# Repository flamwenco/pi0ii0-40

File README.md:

# pi0ii0-40
Open source, RP2040 based pcb for the [M0ii040](https://booth.pm/ja/items/4407257).

Supported layout options:

## Production files

The current version of this pcb that supports all above layouts has been ordered and confirmed to work, but I am not responsible for your orders with a pcb manu. No support will be provided, order at your own risk.

## Special Thanks
[SST60](https://github.com/dededecline/SST60), this project heavily lifts the rp2040 wiring from it

[marksard's](https://github.com/marksard/ms_m0ii040pcb) m0ii040 pcb, used to sanity check my edge cuts

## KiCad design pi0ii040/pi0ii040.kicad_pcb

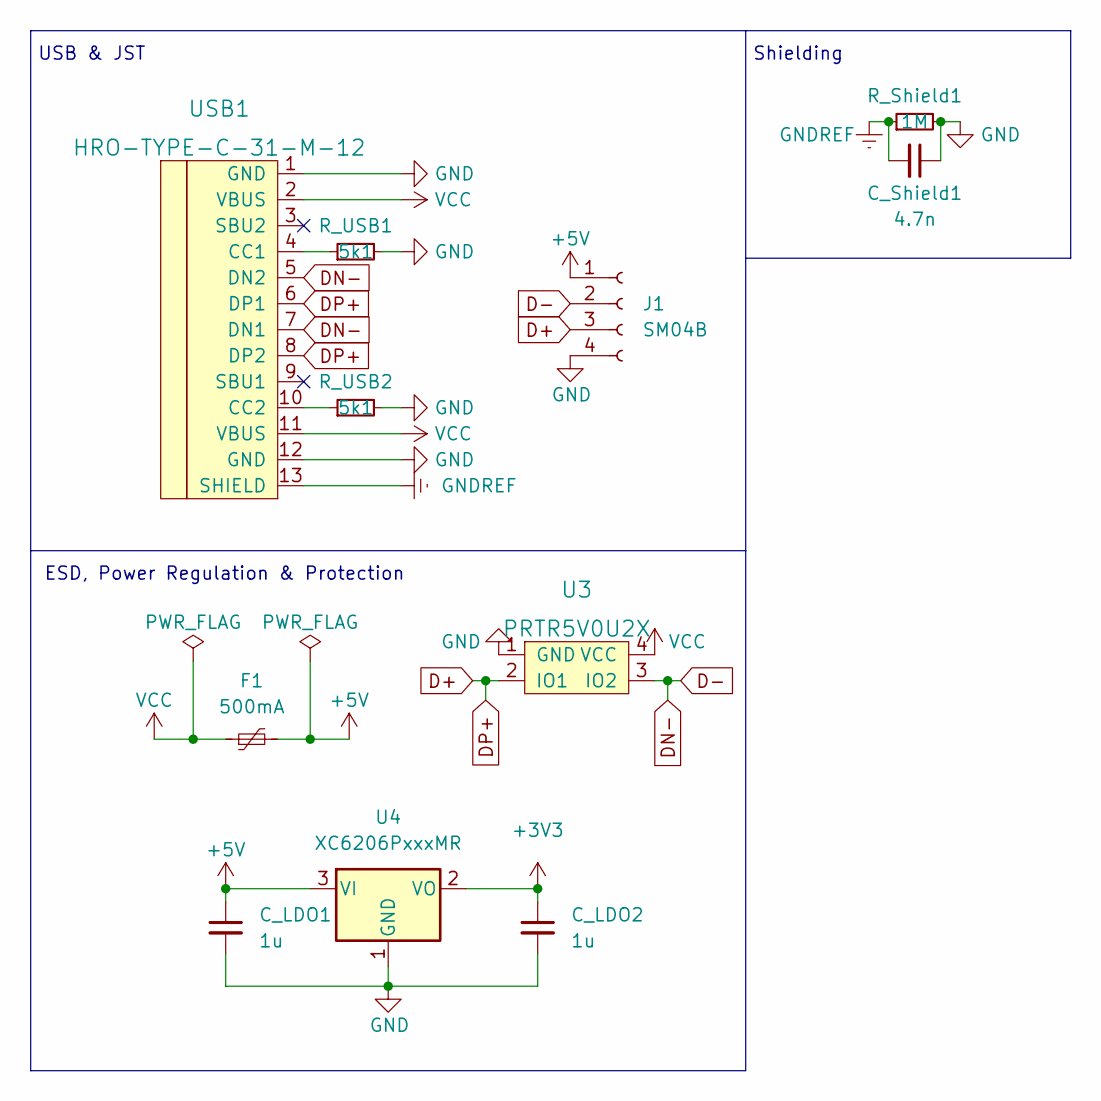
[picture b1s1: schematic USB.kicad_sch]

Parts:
C_LDO1, C_LDO2: 1u; C_0402_1005Metric
C_Shield1: 4.7n; C_0402_1005Metric
F1: 500mA; Fuse_0805_2012Metric
J1: SM04B; JST_SH_SM04B-SRSS-TB_1x04-1MP_P1.00mm_Horizontal
R_Shield1: 1M; R_0402_1005Metric
R_USB1, R_USB2: 5k1; R_0402_1005Metric
U3: PRTR5V0U2X; SOT143B
U4: XC6206PxxxMR; SOT-23
USB1: HRO-TYPE-C-31-M-12; HRO-TYPE-C-31-M-12-Assembly

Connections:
+3V3: C_LDO2.1, U4.2 (VO); also elsewhere on the board
+5V: C_LDO1.1, F1.2, J1.1, U4.3 (VI)
D+: J1.3, U3.2 (IO1), USB1.6 (DP1), USB1.8 (DP2); also elsewhere on the board
D-: J1.2, U3.3 (IO2), USB1.5 (DN2), USB1.7 (DN1); also elsewhere on the board
GND: C_LDO1.2, C_LDO2.2, C_Shield1.1, J1.4, R_Shield1.2, R_USB1.2, R_USB2.2, U3.1 (GND), U4.1 (GND), USB1.1 (GND), USB1.12 (GND); also elsewhere on the board
GNDREF: C_Shield1.2, R_Shield1.1, USB1.13 (SHIELD)
unnamed: R_USB1.1, USB1.4 (CC1)
unnamed: R_USB2.1, USB1.10 (CC2)
VCC: F1.1, U3.4 (VCC), USB1.2 (VBUS), USB1.11 (VBUS)

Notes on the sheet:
Shielding
ESD, Power Regulation & Protection
USB & JST

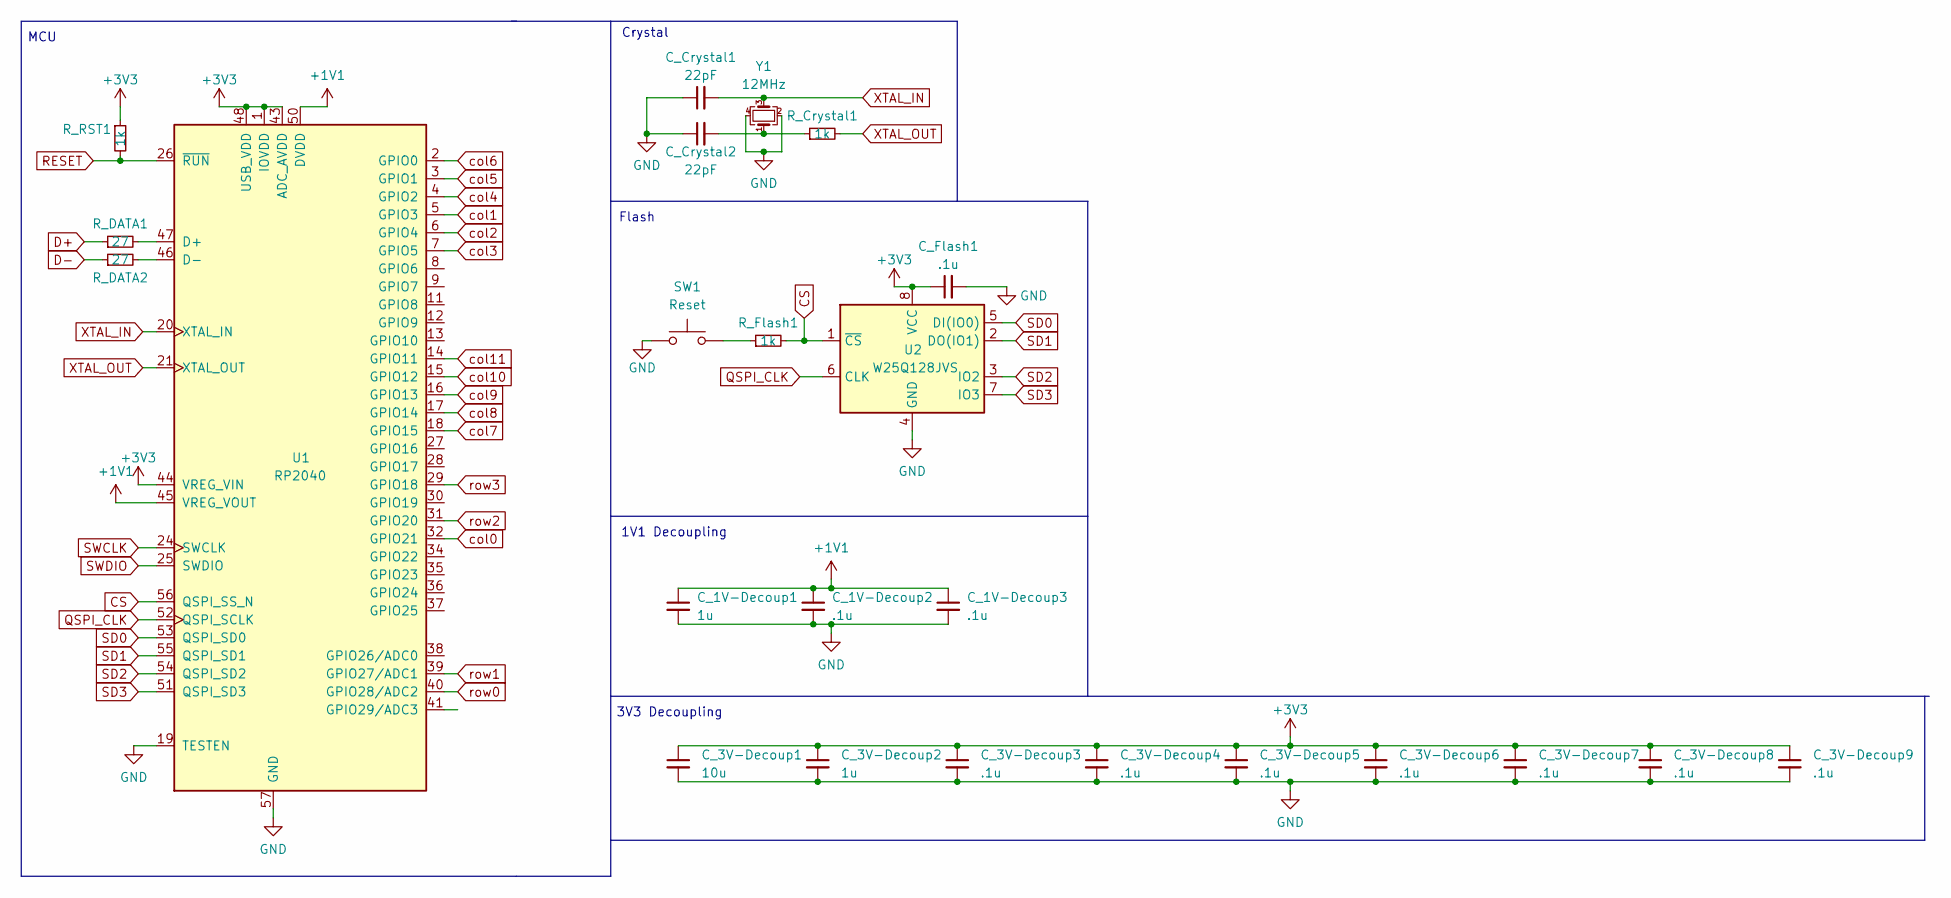
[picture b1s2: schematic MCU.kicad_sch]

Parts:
C_1V-Decoup1, C_3V-Decoup2: 1u; C_0402_1005Metric
C_1V-Decoup2, C_1V-Decoup3, C_3V-Decoup3, C_3V-Decoup4, C_3V-Decoup5, C_3V-Decoup6, C_3V-Decoup7, C_3V-Decoup8, C_3V-Decoup9: .1u; C_0402_1005Metric
C_3V-Decoup1: 10u; C_0402_1005Metric
C_Crystal1, C_Crystal2: 22pF; C_0402_1005Metric
C_Flash1: .1u; C_0402_1005Metric
R_Crystal1: 1k; R_0402_1005Metric
R_DATA1, R_DATA2: 27; R_0402_1005Metric
R_Flash1: 1k; R_0402_1005Metric
R_RST1: 1k; R_0402_1005Metric
SW1: Reset; PinHeader_1x02_P1.27mm_Vertical
U1: RP2040; RP2040-QFN-56
U2: W25Q128JVS; SOIC-8_5.23x5.23mm_P1.27mm
Y1: 12MHz; Crystal_SMD_3225-4Pin_3.2x2.5mm

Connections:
+1V1: C_1V-Decoup1.1, C_1V-Decoup2.1, C_1V-Decoup3.1, U1.23 (DVDD), U1.45 (VREG_VOUT), U1.50 (DVDD)
+3V3: C_3V-Decoup1.1, C_3V-Decoup2.1, C_3V-Decoup3.1, C_3V-Decoup4.1, C_3V-Decoup5.1, C_3V-Decoup6.1, C_3V-Decoup7.1, C_3V-Decoup8.1, C_3V-Decoup9.1, C_Flash1.1, R_RST1.1, U1.1 (IOVDD), U1.10 (IOVDD), U1.22 (IOVDD), U1.33 (IOVDD), U1.42 (IOVDD), U1.43 (ADC_AVDD), U1.44 (VREG_VIN), U1.48 (USB_VDD), U1.49 (IOVDD), U2.8 (VCC); also elsewhere on the board
CS: R_Flash1.2, U1.56 (QSPI_SS_N), U2.1 (~CS)
D+: R_DATA1.1; also elsewhere on the board
D-: R_DATA2.1; also elsewhere on the board
GND: C_1V-Decoup1.2, C_1V-Decoup2.2, C_1V-Decoup3.2, C_3V-Decoup1.2, C_3V-Decoup2.2, C_3V-Decoup3.2, C_3V-Decoup4.2, C_3V-Decoup5.2, C_3V-Decoup6.2, C_3V-Decoup7.2, C_3V-Decoup8.2, C_3V-Decoup9.2, C_Crystal1.1, C_Crystal2.1, C_Flash1.2, SW1.1, U1.19 (TESTEN), U1.57 (GND), U2.4 (GND), Y1.2, Y1.4; also elsewhere on the board
unnamed: C_Crystal2.2, R_Crystal1.1, Y1.1
unnamed: R_Flash1.1, SW1.2
unnamed: R_DATA1.2, U1.47 (D+)
unnamed: R_DATA2.2, U1.46 (D-)
QSPI_CLK: U1.52 (QSPI_SCLK), U2.6 (CLK)
RESET: R_RST1.2, U1.26 (~RUN); also elsewhere on the board
SD0: U1.53 (QSPI_SD0), U2.5 (DI(IO0))
SD1: U1.55 (QSPI_SD1), U2.2 (DO(IO1))
SD2: U1.54 (QSPI_SD2), U2.3 (IO2)
SD3: U1.51 (QSPI_SD3), U2.7 (IO3)
SWCLK: U1.24 (SWCLK); also elsewhere on the board
SWDIO: U1.25 (SWDIO); also elsewhere on the board
XTAL_IN: C_Crystal1.2, U1.20 (XTAL_IN), Y1.3
XTAL_OUT: R_Crystal1.2, U1.21 (XTAL_OUT)
col0: U1.32 (GPIO21); also elsewhere on the board
col1: U1.5 (GPIO3); also elsewhere on the board
col2: U1.6 (GPIO4); also elsewhere on the board
col3: U1.7 (GPIO5); also elsewhere on the board
col4: U1.4 (GPIO2); also elsewhere on the board
col5: U1.3 (GPIO1); also elsewhere on the board
col6: U1.2 (GPIO0); also elsewhere on the board
col7: U1.18 (GPIO15); also elsewhere on the board
col8: U1.17 (GPIO14); also elsewhere on the board
col9: U1.16 (GPIO13); also elsewhere on the board
col10: U1.15 (GPIO12); also elsewhere on the board
col11: U1.14 (GPIO11); also elsewhere on the board
row0: U1.40 (GPIO28/ADC2); also elsewhere on the board
row1: U1.39 (GPIO27/ADC1); also elsewhere on the board
row2: U1.31 (GPIO20); also elsewhere on the board
row3: U1.29 (GPIO18); also elsewhere on the board

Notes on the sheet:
1V1 Decoupling
MCU
3V3 Decoupling
Crystal
Flash

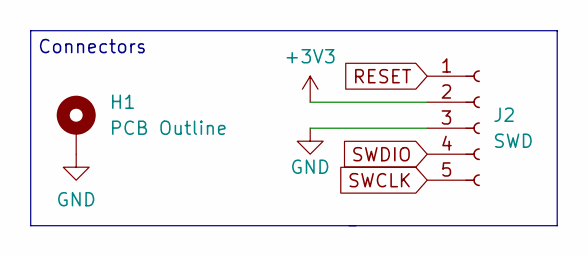
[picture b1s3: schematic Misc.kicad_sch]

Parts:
H1: PCB Outline; m0ii040_PCB_Template_v1.0.1
J2: SWD; PinHeader_1x05_P2.54mm_Vertical

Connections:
+3V3: J2.2; also elsewhere on the board
GND: H1.1, J2.3; also elsewhere on the board
RESET: J2.1; also elsewhere on the board
SWCLK: J2.5; also elsewhere on the board
SWDIO: J2.4; also elsewhere on the board

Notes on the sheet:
Connectors

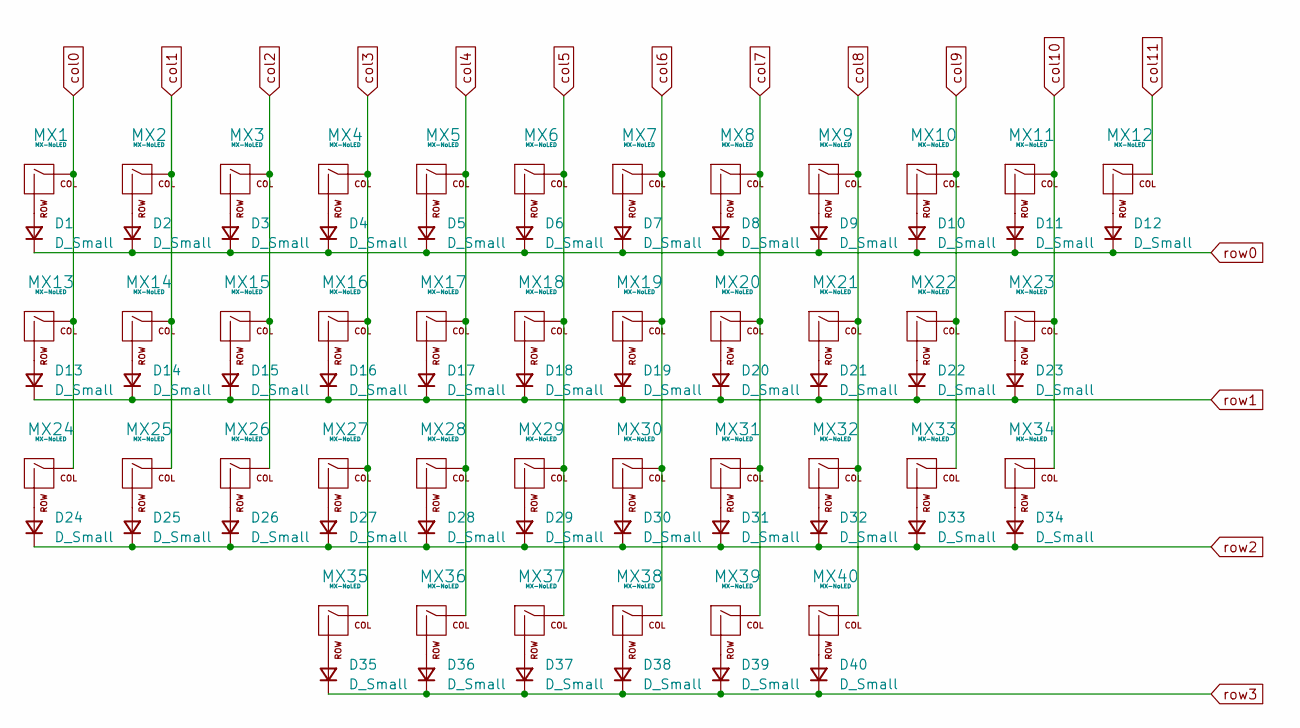
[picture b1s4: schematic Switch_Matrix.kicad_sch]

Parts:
D1, D2, D3, D4, D5, D6, D7, D8, D9, D10, D11, D12, D13, D14, D15, D16, D17, D18, D19, D20, D21, D22, D23, D24, D25, D26, D27, D28, D29, D30, D31, D32, D33, D34, D35, D36, D37, D38, D39, D40: D_Small; D_SOD-123
MX1, MX2, MX3, MX4, MX5, MX6, MX7, MX8, MX9, MX10, MX11, MX12, MX14, MX15, MX16, MX17, MX18, MX19, MX20, MX21, MX22, MX25, MX26, MX27, MX28, MX29, MX30, MX31, MX32, MX33, MX35, MX40: MX-NoLED; MXOnly-1U-NoLED
MX13, MX34, MX36, MX39: MX-NoLED; MXOnly-1.25U-NoLED
MX23, MX24: MX-NoLED; MXOnly-1.75U-NoLED
MX37: MX-NoLED; MXOnly-2.75U-ReversedStabilizers-NoLED
MX38: MX-NoLED; MXOnly-2.25U-ReversedStabilizers-NoLED

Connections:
unnamed: D1.2 (A), MX1.2 (ROW)
unnamed: D2.2 (A), MX2.2 (ROW)
unnamed: D3.2 (A), MX3.2 (ROW)
unnamed: D4.2 (A), MX4.2 (ROW)
unnamed: D5.2 (A), MX5.2 (ROW)
unnamed: D6.2 (A), MX6.2 (ROW)
unnamed: D7.2 (A), MX7.2 (ROW)
unnamed: D8.2 (A), MX8.2 (ROW)
unnamed: D9.2 (A), MX9.2 (ROW)
unnamed: D10.2 (A), MX10.2 (ROW)
unnamed: D11.2 (A), MX11.2 (ROW)
unnamed: D12.2 (A), MX12.2 (ROW)
unnamed: D13.2 (A), MX13.2 (ROW)
unnamed: D14.2 (A), MX14.2 (ROW)
unnamed: D15.2 (A), MX15.2 (ROW)
unnamed: D16.2 (A), MX16.2 (ROW)
unnamed: D17.2 (A), MX17.2 (ROW)
unnamed: D18.2 (A), MX18.2 (ROW)
unnamed: D19.2 (A), MX19.2 (ROW)
unnamed: D20.2 (A), MX20.2 (ROW)
unnamed: D21.2 (A), MX21.2 (ROW)
unnamed: D22.2 (A), MX22.2 (ROW)
unnamed: D23.2 (A), MX23.2 (ROW)
unnamed: D24.2 (A), MX24.2 (ROW)
unnamed: D25.2 (A), MX25.2 (ROW)
unnamed: D26.2 (A), MX26.2 (ROW)
unnamed: D27.2 (A), MX27.2 (ROW)
unnamed: D28.2 (A), MX28.2 (ROW)
unnamed: D29.2 (A), MX29.2 (ROW)
unnamed: D30.2 (A), MX30.2 (ROW)
unnamed: D31.2 (A), MX31.2 (ROW)
unnamed: D32.2 (A), MX32.2 (ROW)
unnamed 41: D33.2 (A), MX33.2 (ROW); also elsewhere on the board
unnamed 42: D34.2 (A), MX34.2 (ROW); also elsewhere on the board
unnamed 43: D35.2 (A), MX35.2 (ROW); also elsewhere on the board
unnamed: D36.2 (A), MX36.2 (ROW)
unnamed 45: D37.2 (A), MX37.2 (ROW); also elsewhere on the board
unnamed: D38.2 (A), MX38.2 (ROW)
unnamed: D39.2 (A), MX39.2 (ROW)
unnamed 48: D40.2 (A), MX40.2 (ROW); also elsewhere on the board
col0: MX1.1 (COL), MX13.1 (COL), MX24.1 (COL); also elsewhere on the board
col1: MX2.1 (COL), MX14.1 (COL), MX25.1 (COL); also elsewhere on the board
col2: MX3.1 (COL), MX15.1 (COL), MX26.1 (COL); also elsewhere on the board
col3: MX4.1 (COL), MX16.1 (COL), MX27.1 (COL), MX35.1 (COL); also elsewhere on the board
col4: MX5.1 (COL), MX17.1 (COL), MX28.1 (COL), MX36.1 (COL); also elsewhere on the board
col5: MX6.1 (COL), MX18.1 (COL), MX29.1 (COL), MX37.1 (COL); also elsewhere on the board
col6: MX7.1 (COL), MX19.1 (COL), MX30.1 (COL), MX38.1 (COL); also elsewhere on the board
col7: MX8.1 (COL), MX20.1 (COL), MX31.1 (COL), MX39.1 (COL); also elsewhere on the board
col8: MX9.1 (COL), MX21.1 (COL), MX32.1 (COL), MX40.1 (COL); also elsewhere on the board
col9: MX10.1 (COL), MX22.1 (COL), MX33.1 (COL); also elsewhere on the board
col10: MX11.1 (COL), MX23.1 (COL), MX34.1 (COL); also elsewhere on the board
col11: MX12.1 (COL); also elsewhere on the board
row0: D1.1 (K), D2.1 (K), D3.1 (K), D4.1 (K), D5.1 (K), D6.1 (K), D7.1 (K), D8.1 (K), D9.1 (K), D10.1 (K), D11.1 (K), D12.1 (K); also elsewhere on the board
row1: D13.1 (K), D14.1 (K), D15.1 (K), D16.1 (K), D17.1 (K), D18.1 (K), D19.1 (K), D20.1 (K), D21.1 (K), D22.1 (K), D23.1 (K); also elsewhere on the board
row2: D24.1 (K), D25.1 (K), D26.1 (K), D27.1 (K), D28.1 (K), D29.1 (K), D30.1 (K), D31.1 (K), D32.1 (K), D33.1 (K), D34.1 (K); also elsewhere on the board
row3: D35.1 (K), D36.1 (K), D37.1 (K), D38.1 (K), D39.1 (K), D40.1 (K); also elsewhere on the board

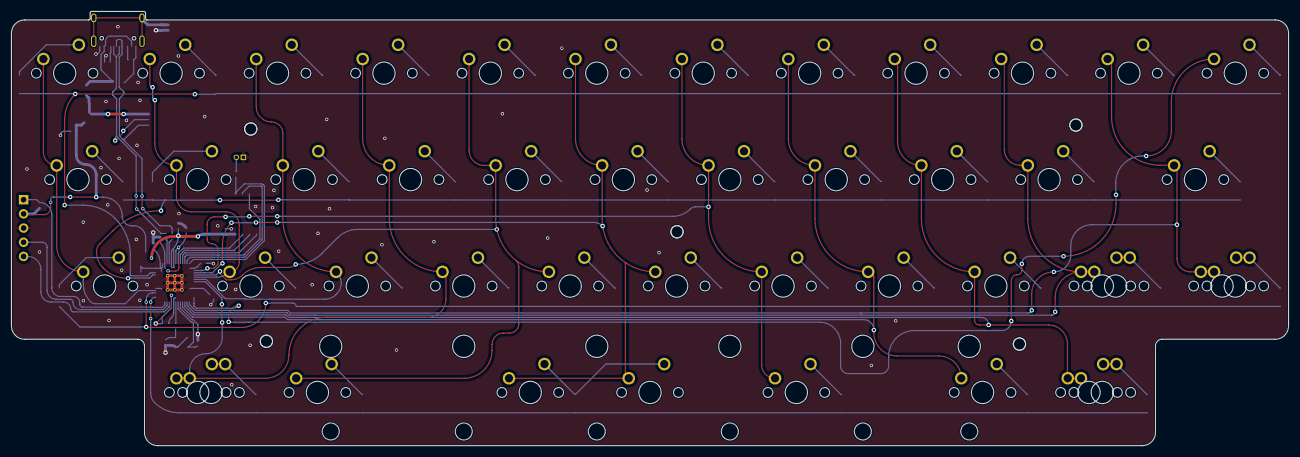
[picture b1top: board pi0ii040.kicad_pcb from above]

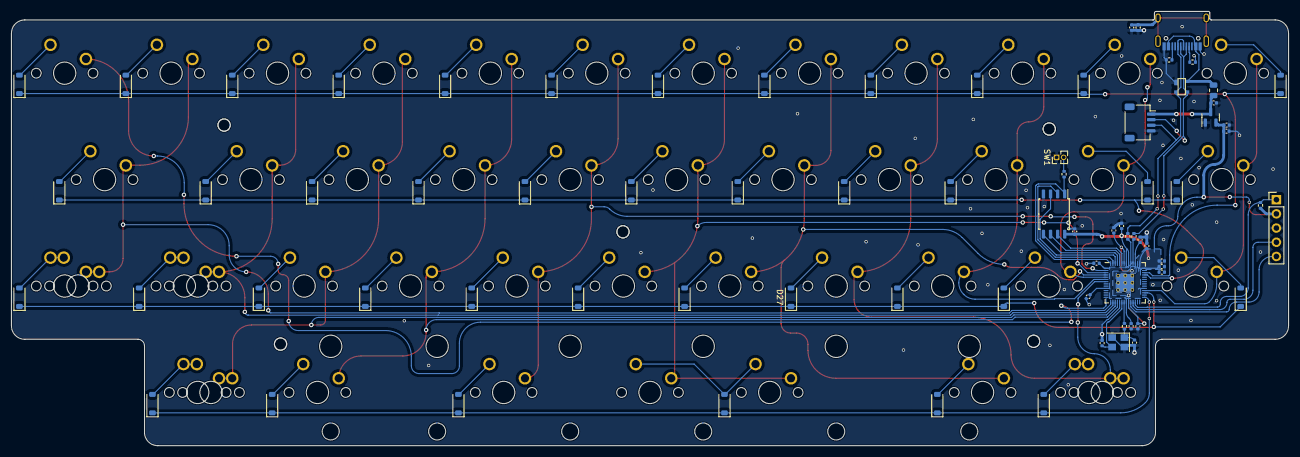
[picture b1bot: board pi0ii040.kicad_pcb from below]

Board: 2 copper layers, 228.6 x 77.7 mm, 122 parts (76 on the bottom side), 81 nets.

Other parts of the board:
MX33#2, MX34#2, MX35#2, MX40#2: MX-NoLED; MXOnly-1U-NoLED
MX37#2: MX-NoLED; MXOnly-2.75U-ReversedStabilizers-NoLED

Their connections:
unnamed 41: MX33#2.2 (ROW); also elsewhere on the board
unnamed 42: MX34#2.2 (ROW); also elsewhere on the board
unnamed 43: MX35#2.2 (ROW); also elsewhere on the board
unnamed 45: MX37#2.2 (ROW); also elsewhere on the board
unnamed 48: MX40#2.2 (ROW); also elsewhere on the board
col3: MX35#2.1 (COL); also elsewhere on the board
col5: MX37#2.1 (COL); also elsewhere on the board
col8: MX40#2.1 (COL); also elsewhere on the board
col9: MX33#2.1 (COL); also elsewhere on the board
col10: MX34#2.1 (COL); also elsewhere on the board

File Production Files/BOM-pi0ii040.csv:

Comment,Designator,Footprint,LCSC
1k,"R_Crystal1,R_Flash1,R_RST1",R_0402_1005Metric,C11702
PRTR5V0U2X,U3,SOT143B,C12333
.1u,"C_1V-Decoup2,C_1V-Decoup3,C_3V-Decoup3,C_3V-Decoup4,C_3V-Decoup5,C_3V-Decoup6,C_3V-Decoup7,C_3V-Decoup8,C_3V-Decoup9,C_Flash1",C_0402_1005Metric,C1525
10u,C_3V-Decoup1,C_0402_1005Metric,C15525
22pF,"C_Crystal1,C_Crystal2",C_0402_1005Metric,C1555
HRO-TYPE-C-31-M-12,USB1,HRO-TYPE-C-31-M-12-Assembly,C165948
27,"R_DATA1,R_DATA2",R_0402_1005Metric,C203147
RP2040,U1,RP2040-QFN-56,C2040
4.7n,C_Shield1,C_0402_1005Metric,C237221
5k1,"R_USB1,R_USB2",R_0402_1005Metric,C25905
1M,R_Shield1,R_0402_1005Metric,C26083
1u,"C_1V-Decoup1,C_3V-Decoup2,C_LDO1,C_LDO2",C_0402_1005Metric,C52923
XC6206PxxxMR,U4,SOT-23,C5446
D_Small,"D1,D10,D11,D12,D13,D14,D15,D16,D17,D18,D19,D2,D20,D21,D22,D23,D24,D25,D26,D27,D28,D29,D3,D30,D31,D32,D33,D34,D35,D36,D37,D38,D39,D4,D40,D5,D6,D7,D8,D9",D_SOD-123,C64898
12MHz,Y1,Crystal_SMD_3225-4Pin_3.2x2.5mm,C9002
W25Q128JVS,U2,SOIC-8_5.23x5.23mm_P1.27mm,C97521
500mA,F1,Fuse_0805_2012Metric,

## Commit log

2023-04-17 Add submodules, start schematic
2023-04-17 More submodule
2023-04-18 Finish? pcb
2023-04-21 More pcb work and create plate
2023-04-27 Create production files folder
2023-04-27 Firmware files
2023-04-27 Add license
